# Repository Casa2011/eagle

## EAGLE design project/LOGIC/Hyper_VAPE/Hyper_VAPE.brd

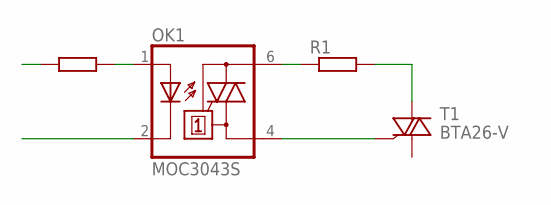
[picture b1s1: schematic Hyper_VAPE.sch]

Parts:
OK1: MOC3043S; DIL6-SMD
R1: R-EU_0411/3V; 0411V
R3: R0805
T1: BTA26-V; TOP3S-1

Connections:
unnamed: OK1.4 (A1), T1.G
unnamed: OK1.6 (A2), R1.1
unnamed: R1.2, T1.A2
unnamed: OK1.1 (A), R3.2

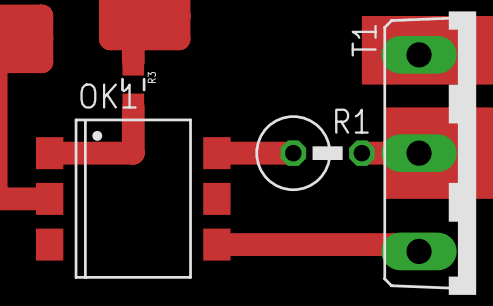
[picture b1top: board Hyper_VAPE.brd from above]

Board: 2 copper layers, 4 parts (0 on the bottom side), 4 nets.

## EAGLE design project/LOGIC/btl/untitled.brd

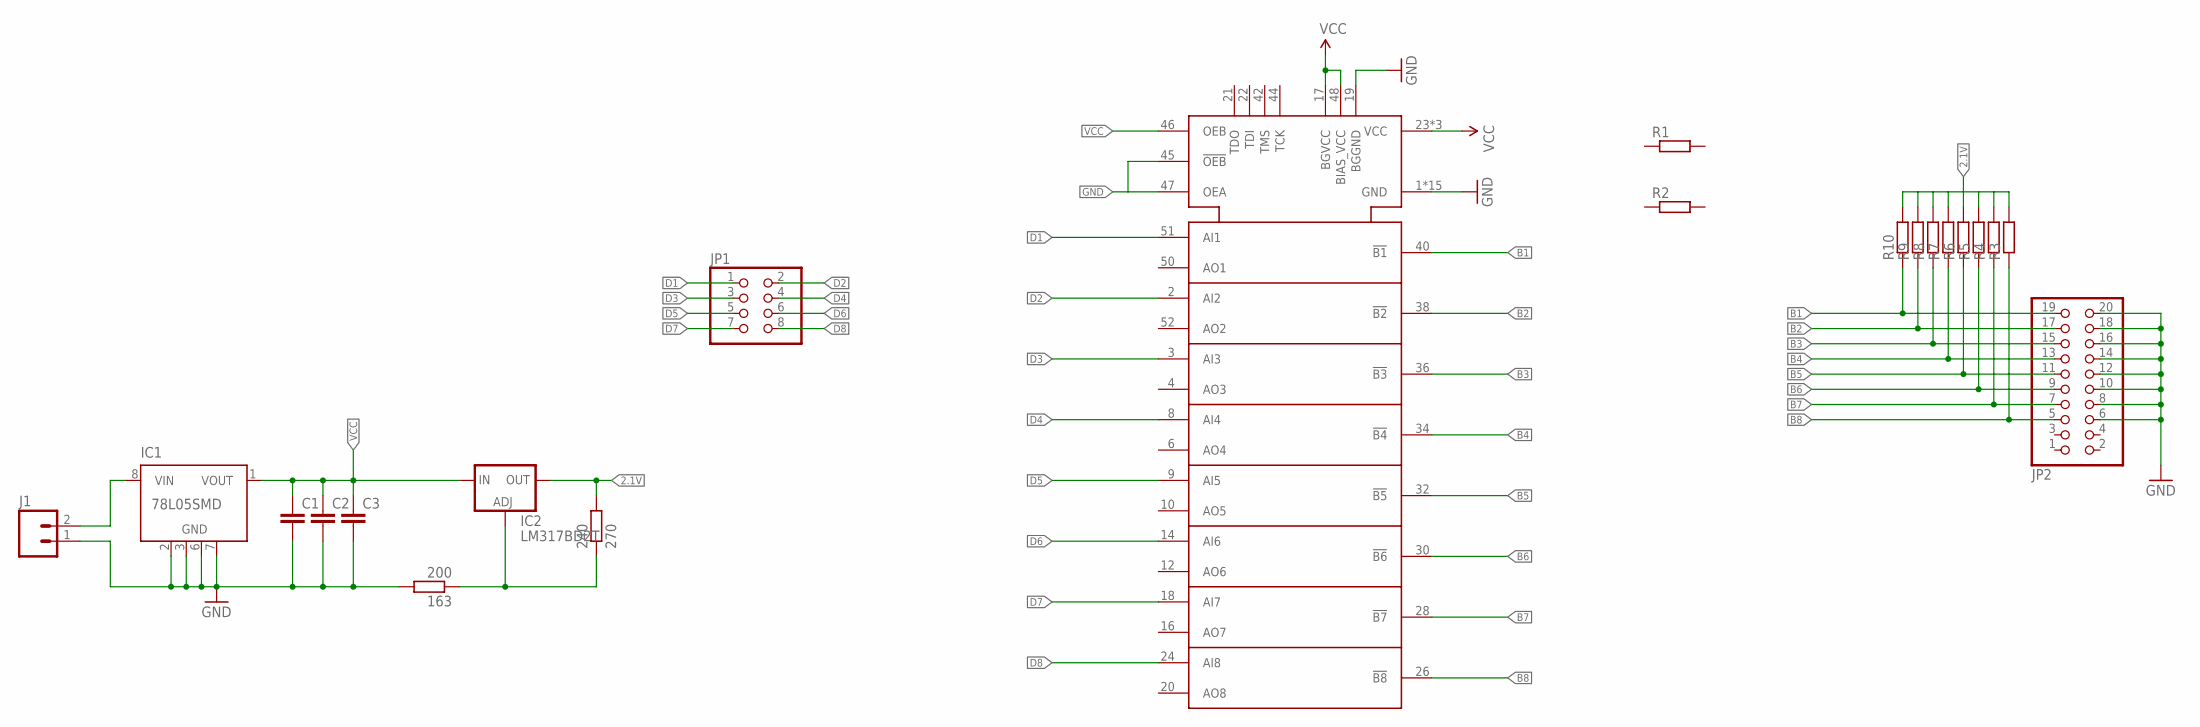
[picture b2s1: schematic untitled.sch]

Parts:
163: 200; R0805
240: 270; R0805
C1, C2, C3: CC0805; C0805
IC1: 78L05SMD; SO08
IC2: LM317BD2T; D2PACK
J1: M02LOCK_LONGPADS; 1X02_LOCK_LONGPADS
JP1: PINHD-2X04_2.54-SMD; 2X04SMD
JP2: PINHD-2X10_2.54-SMD; 2X10SMD
R1, R2, R3, R4, R5, R6, R7, R8, R9, R10: R0805
U$1: SN74FB2050; TQFP-10X10-52

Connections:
2.1V: 240.2, IC2.2 (OUT), R3.2, R4.2, R5.2, R6.2, R7.2, R8.2, R9.2, R10.2
B1: JP2.19, R10.1, U$1.40 (!B1)
B2: JP2.17, R9.1, U$1.38 (!B2)
B3: JP2.15, R8.1, U$1.36 (!B3)
B4: JP2.13, R7.1, U$1.34 (!B4)
B5: JP2.11, R6.1, U$1.32 (!B5)
B6: JP2.9, R5.1, U$1.30 (!B6)
B7: JP2.7, R4.1, U$1.28 (!B7)
B8: JP2.5, R3.1, U$1.26 (!B8)
D1: JP1.1, U$1.51 (AI1)
D2: JP1.2, U$1.2 (AI2)
D3: JP1.3, U$1.3 (AI3)
D4: JP1.4, U$1.8 (AI4)
D5: JP1.5, U$1.9 (AI5)
D6: JP1.6, U$1.14 (AI6)
D7: JP1.7, U$1.18 (AI7)
D8: JP1.8, U$1.24 (AI8)
GND: 163.2, C1.2, C2.2, C3.2, IC1.2 (GND), IC1.3 (GND), IC1.6 (GND), IC1.7 (GND), J1.1, JP2.6, JP2.8, JP2.10, JP2.12, JP2.14, JP2.16, JP2.18, JP2.20, U$1.1 (GND), U$1.5 (GND), U$1.7 (GND), U$1.11 (GND), U$1.13 (GND), U$1.15 (GND), U$1.19 (BGGND), U$1.25 (GND), U$1.27 (GND), U$1.29 (GND), U$1.31 (GND), U$1.33 (GND), U$1.35 (GND), U$1.37 (GND), U$1.39 (GND), U$1.41 (GND), U$1.45 (!OEB), U$1.47 (OEA)
unnamed: IC1.8 (VIN), J1.2
unnamed: 163.1, 240.1, IC2.1 (ADJ)
VCC: C1.1, C2.1, C3.1, IC1.1 (VOUT), IC2.3 (IN), U$1.17 (BGVCC), U$1.23 (VCC), U$1.43 (VCC), U$1.46 (OEB), U$1.48 (BIAS_VCC), U$1.49 (VCC)

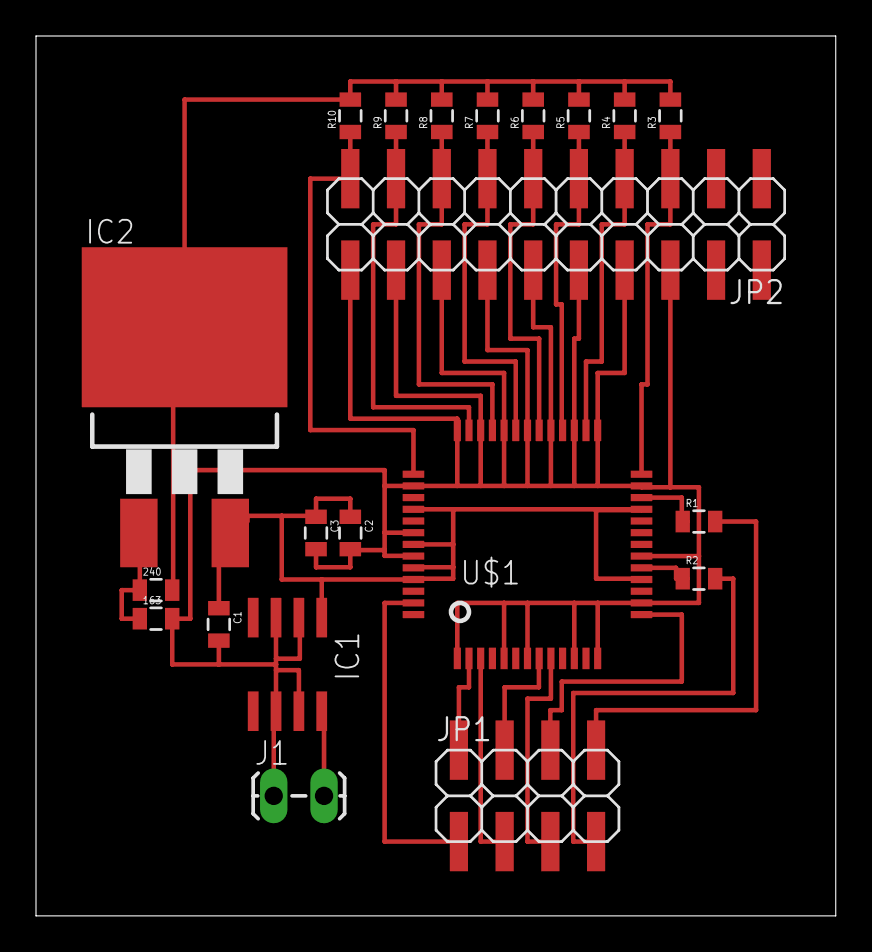
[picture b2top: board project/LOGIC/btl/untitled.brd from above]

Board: 2 copper layers, 44.4 x 48.9 mm, 21 parts (0 on the bottom side), 21 nets.

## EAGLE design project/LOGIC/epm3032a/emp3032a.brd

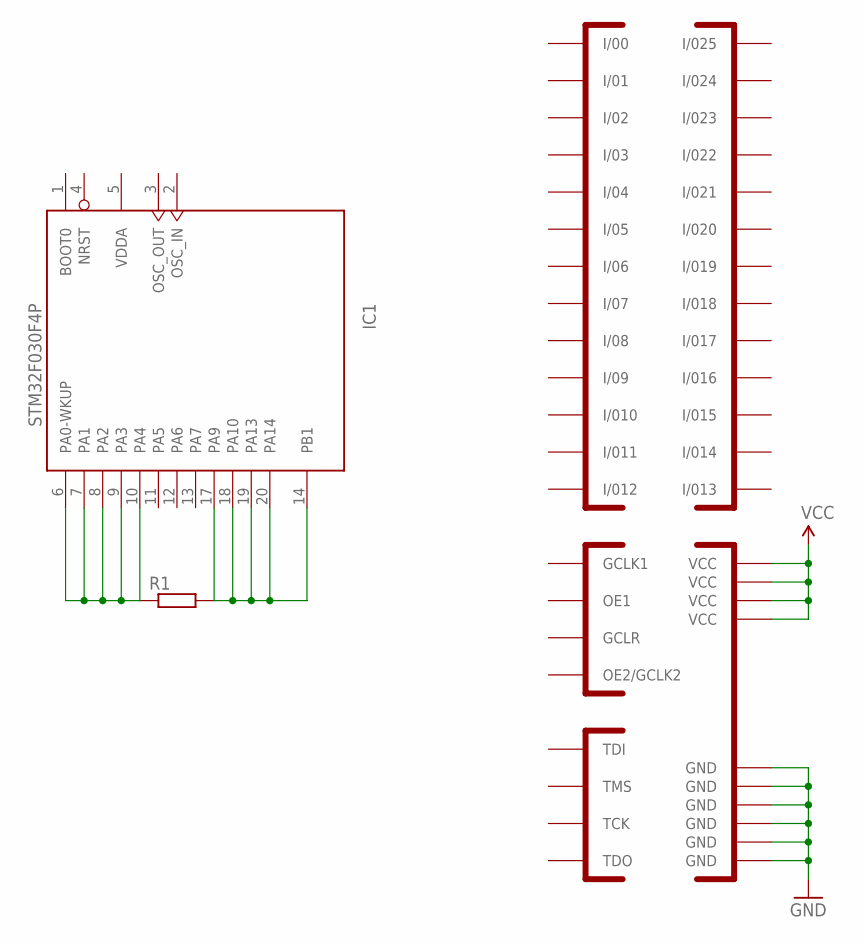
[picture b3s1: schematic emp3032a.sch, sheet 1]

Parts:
IC1: STM32F030F4P; TSSOP20-I
R1: R1206
U$1: EPM3032; TQFP44

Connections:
GCLK1: U$1.37 (GCLK1)
GCLR: U$1.39 (GCLR)
GND: U$1.4 (GND), U$1.11 (GND), U$1.16 (GND), U$1.24 (GND), U$1.30 (GND), U$1.36 (GND); also elsewhere on the board
I/00: U$1.2 (I/00)
I/01: U$1.5 (I/01)
I/02: U$1.6 (I/02)
I/03: U$1.12 (I/03)
I/04: U$1.13 (I/04)
I/05: U$1.14 (I/05)
I/06: U$1.15 (I/06)
I/07: U$1.25 (I/07)
I/08: U$1.44 (I/08)
I/09: U$1.43 (I/09)
I/010: U$1.42 (I/010)
I/011: U$1.35 (I/011)
I/012: U$1.34 (I/012)
I/013: U$1.28 (I/013)
I/014: U$1.27 (I/014)
I/015: U$1.33 (I/015)
I/016: U$1.21 (I/016)
I/017: U$1.22 (I/017)
I/018: U$1.23 (I/018)
I/019: U$1.31 (I/019)
I/020: U$1.18 (I/020)
I/021: U$1.19 (I/021)
I/022: U$1.8 (I/022)
I/023: U$1.20 (I/023)
I/024: U$1.10 (I/024)
I/025: U$1.3 (I/025)
unnamed: IC1.6 (PA0-WKUP), IC1.7 (PA1), IC1.8 (PA2), IC1.9 (PA3), IC1.10 (PA4), R1.1
unnamed: IC1.14 (PB1), IC1.17 (PA9), IC1.18 (PA10), IC1.19 (PA13), IC1.20 (PA14), R1.2
OE1: U$1.38 (OE1)
OE2/GCLK2: U$1.40 (OE2/GCLK2)
TCK: U$1.26 (TCK)
TDI: U$1.1 (TDI)
TDO: U$1.32 (TDO)
TMS: U$1.7 (TMS)
VCC: U$1.9 (VCC), U$1.17 (VCC), U$1.29 (VCC), U$1.41 (VCC)
VDD: IC1.16 (VDD)
VDDA: IC1.5 (VDDA)
VSS: IC1.15 (VSS)

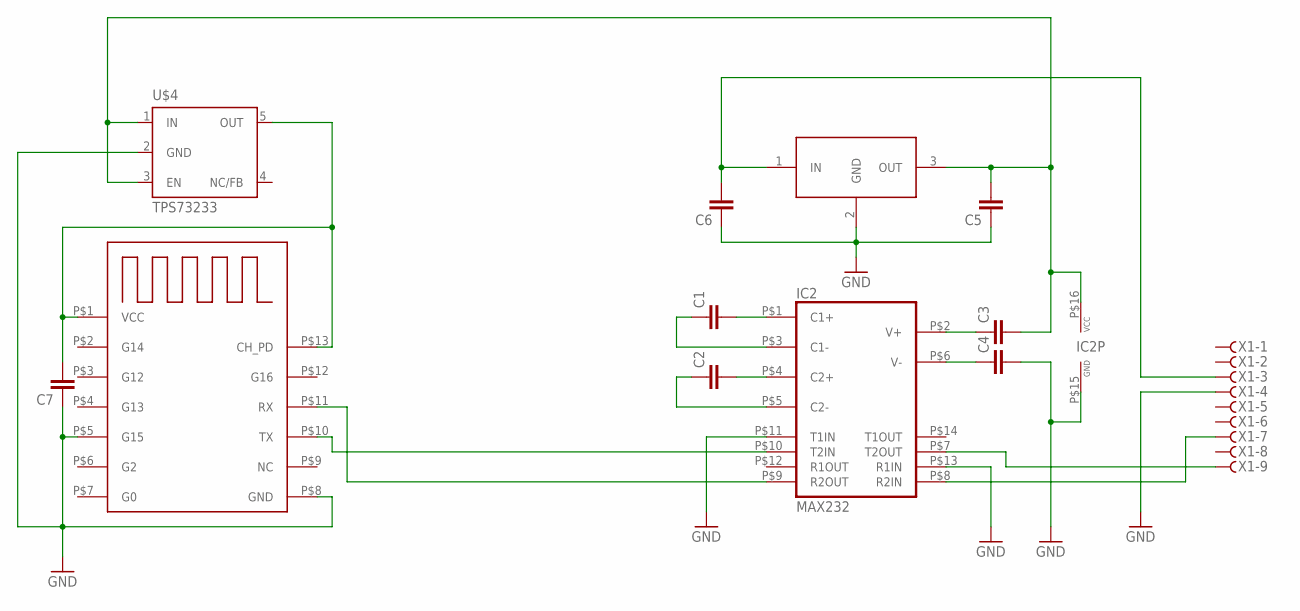
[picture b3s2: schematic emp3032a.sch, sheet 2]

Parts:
C1, C2, C3, C4, C5, C6, C7: C-EUC1206K; C1206K
IC2: MAX232; DIL16
U$2: ESP03
U$3: LM78M05BG; DPACK
U$4: TPS73233; SOT23-DBV
X1: F09HS; F09H

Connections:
GND: C4.2, C5.1, C6.1, C7.1, IC2.P$11 (T1IN), IC2.P$13 (R1IN), IC2.P$15 (GND), U$2.P$5 (G15), U$2.P$8 (GND), U$3.2 (GND), U$4.2 (GND), X1.4; also elsewhere on the board
unnamed: C2.2, IC2.P$4 (C2+)
unnamed: C2.1, IC2.P$5 (C2-)
unnamed: C1.2, IC2.P$1 (C1+)
unnamed: C1.1, IC2.P$3 (C1-)
unnamed: C3.1, IC2.P$2 (V+)
unnamed: C4.1, IC2.P$6 (V-)
unnamed: IC2.P$9 (R2OUT), U$2.P$11 (RX)
unnamed: IC2.P$7 (T2OUT), X1.9
unnamed: IC2.P$8 (R2IN), X1.7
unnamed: C6.2, U$3.1 (IN), X1.3
unnamed: IC2.P$10 (T2IN), U$2.P$10 (TX)
unnamed: C7.2, U$2.P$1 (VCC), U$2.P$13 (CH_PD), U$4.5 (OUT)
unnamed: C3.2, C5.2, IC2.P$16 (VCC), U$3.3 (OUT), U$4.1 (IN), U$4.3 (EN)

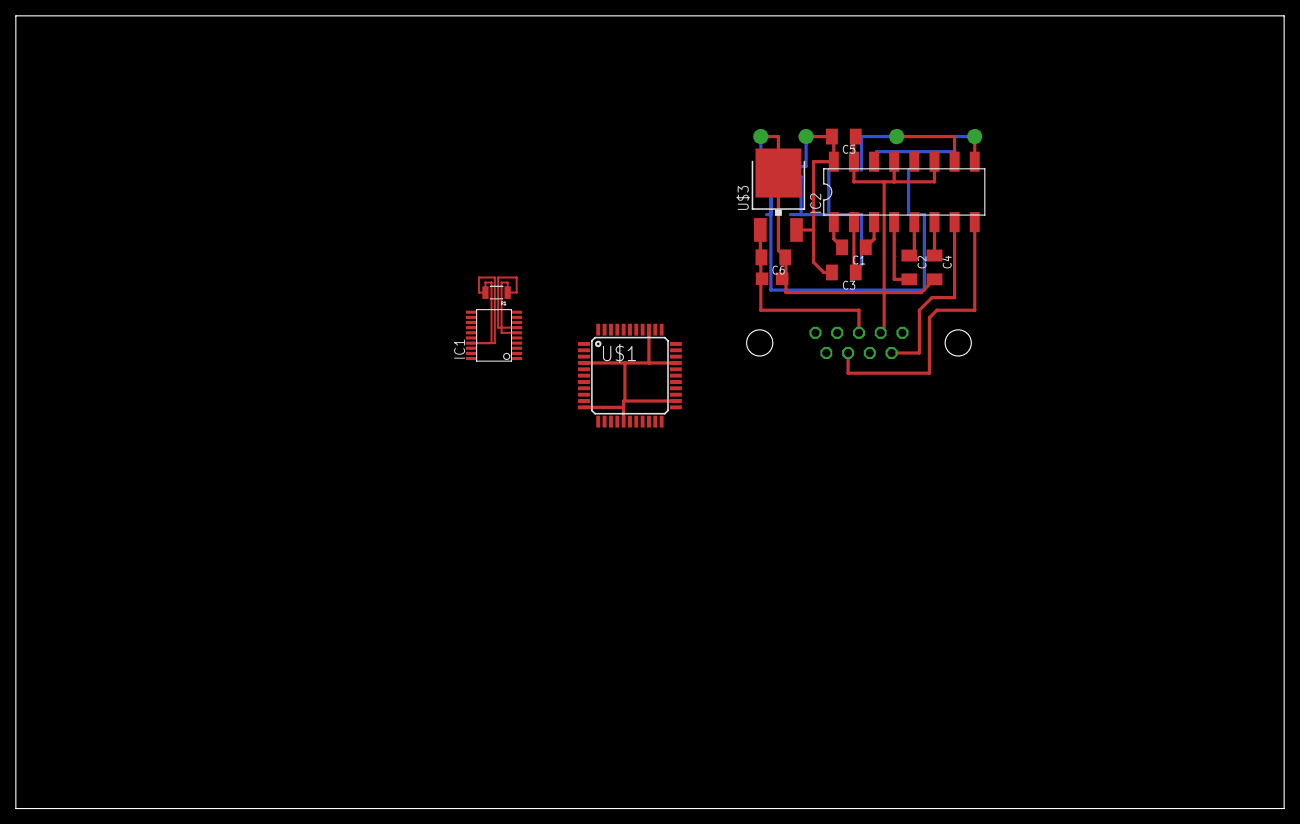
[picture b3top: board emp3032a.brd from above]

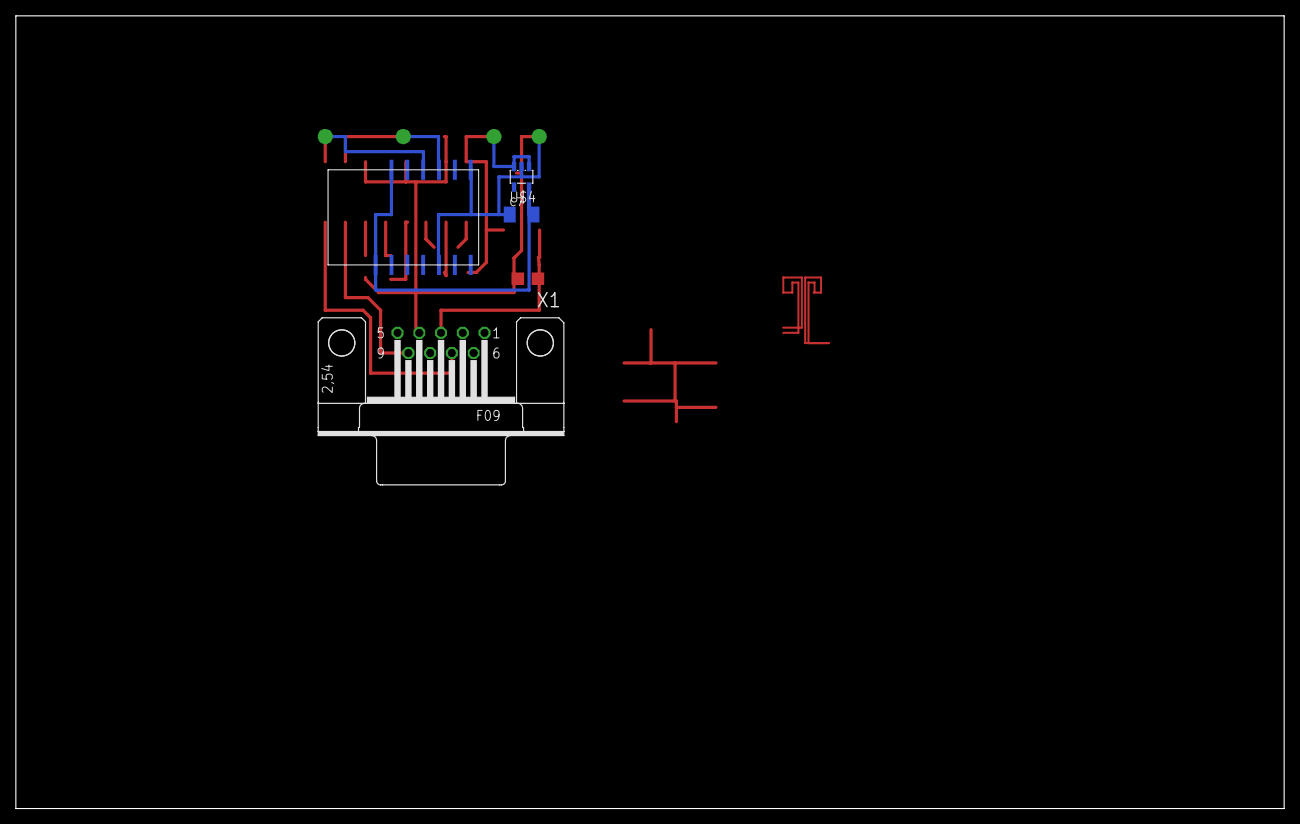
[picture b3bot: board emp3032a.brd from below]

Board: 2 copper layers, 160.0 x 100.0 mm, 15 parts (4 on the bottom side), 17 nets.

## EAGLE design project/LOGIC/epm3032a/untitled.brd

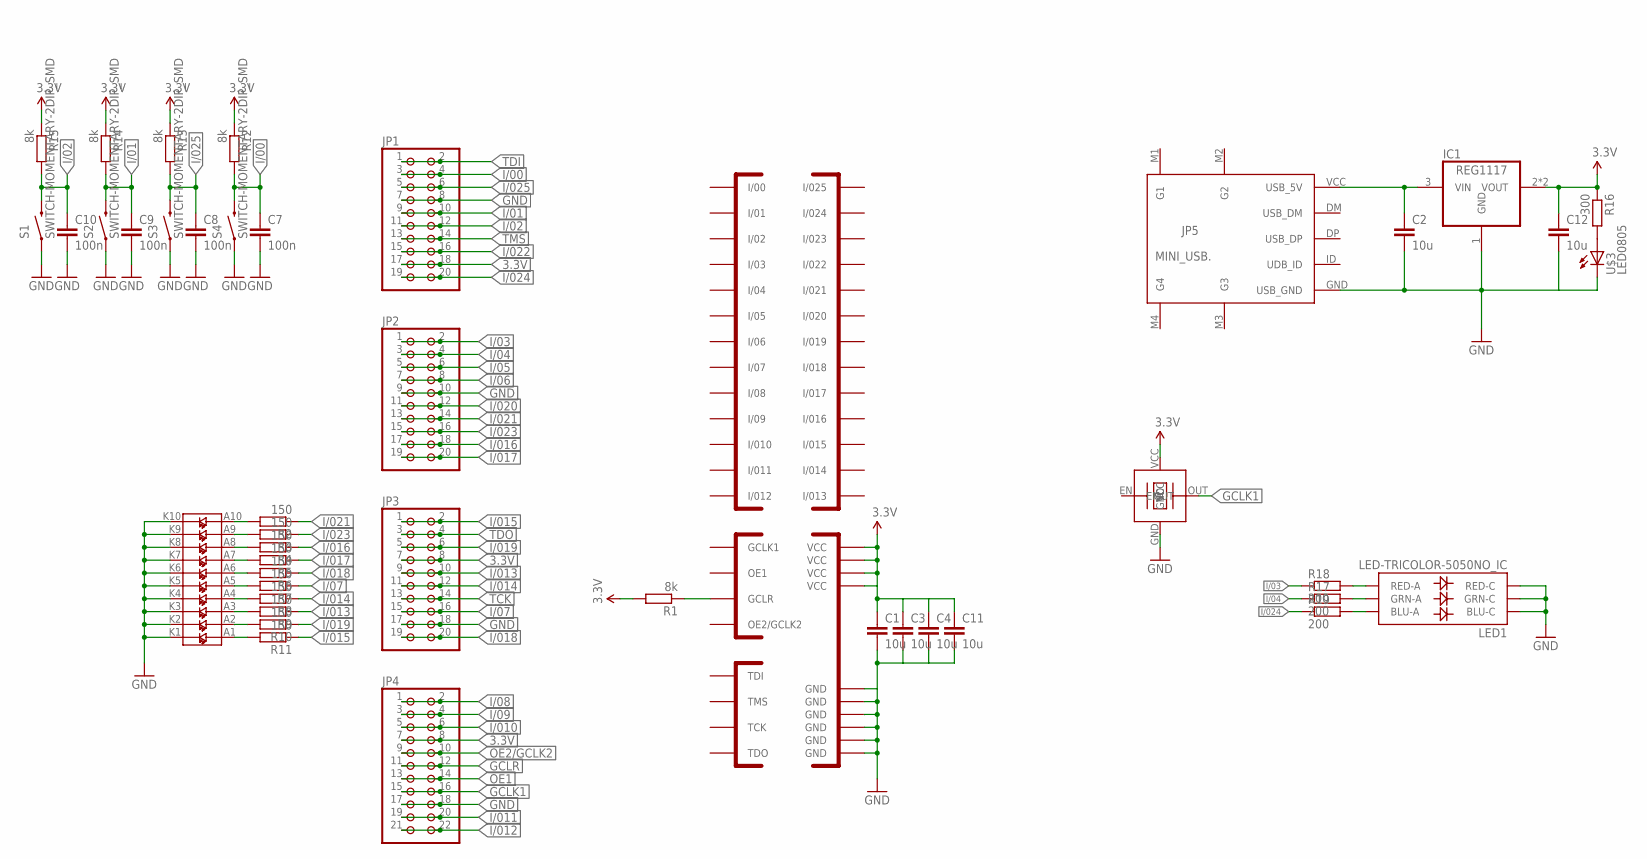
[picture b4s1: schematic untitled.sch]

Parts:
C1, C4: 10u; 0805
C2, C3, C11, C12: 10u; C0805
C7, C8, C9, C10: 100n; C0603
IC1: REG1117; SOT223
JP1, JP2, JP3: PINHD-2X10_2.54-SMD; 2X10SMD
JP4: PINHD-2X11_2.54-SMD; 2X11SMD
JP5: MINI_USB.; 32005-201
LED1: LED-TRICOLOR-5050NO_IC; LED-TRICOLOR-5050
QG1: TXC-BA; 7X5
R1, R12, R13, R14, R15: 8k; 0603
R2, R3, R4, R5, R6, R7, R8, R9, R10, R11: 150; 0603
R16: 300; 0603
R17, R18, R19: 200; 0603
S1, S2, S3, S4: SWITCH-MOMENTARY-2DIP_SMD; DIP_SMD
U$1: EPM3032; TQFP44
U$2: 10LED
U$3: LED0805; 0805-LED

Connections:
3.3V: C1.1, C3.1, C4.1, C11.1, C12.1, IC1.2 (VOUT), IC1.4 (VOUT), JP1.17, JP1.18, JP3.7, JP3.8, JP4.7, JP4.8, QG1.VCC, R1.2, R12.1, R13.1, R14.1, R15.1, R16.1, U$1.9 (VCC), U$1.17 (VCC), U$1.29 (VCC), U$1.41 (VCC)
5V: C2.1, IC1.3 (VIN), JP5.VCC (USB_5V)
GCLK1: JP4.15, JP4.16, QG1.OUT, U$1.37 (GCLK1)
GCLR: JP4.11, JP4.12, R1.1, U$1.39 (GCLR)
GND: C1.2, C2.2, C3.2, C4.2, C7.2, C8.2, C9.2, C10.2, C11.2, C12.2, IC1.1 (GND), JP1.7, JP1.8, JP2.9, JP2.10, JP3.17, JP3.18, JP4.17, JP4.18, JP5.GND (USB_GND), LED1.4 (BLU-C), LED1.5 (RED-C), LED1.6 (GRN-C), QG1.GND, S1.P$1, S1.P$2, S2.P$1, S2.P$2, S3.P$1, S3.P$2, S4.P$1, S4.P$2, U$1.4 (GND), U$1.11 (GND), U$1.16 (GND), U$1.24 (GND), U$1.30 (GND), U$1.36 (GND), U$2.K1, U$2.K2, U$2.K3, U$2.K4, U$2.K5, U$2.K6, U$2.K7, U$2.K8, U$2.K9, U$2.K10, U$3.C
I/00: C7.1, JP1.3, JP1.4, R12.2, S4.P$3, S4.P$4, U$1.2 (I/00)
I/01: C9.1, JP1.9, JP1.10, R14.2, S2.P$3, S2.P$4, U$1.5 (I/01)
I/02: C10.1, JP1.11, JP1.12, R15.2, S1.P$3, S1.P$4, U$1.6 (I/02)
I/03: JP2.1, JP2.2, R18.1, U$1.12 (I/03)
I/04: JP2.3, JP2.4, R17.1, U$1.13 (I/04)
I/05: JP2.5, JP2.6, U$1.14 (I/05)
I/06: JP2.7, JP2.8, U$1.15 (I/06)
I/07: JP3.15, JP3.16, R7.1, U$1.25 (I/07)
I/08: JP4.1, JP4.2, U$1.44 (I/08)
I/09: JP4.3, JP4.4, U$1.43 (I/09)
I/010: JP4.5, JP4.6, U$1.42 (I/010)
I/011: JP4.19, JP4.20, U$1.35 (I/011)
I/012: JP4.21, JP4.22, U$1.34 (I/012)
I/013: JP3.9, JP3.10, R9.1, U$1.28 (I/013)
I/014: JP3.11, JP3.12, R8.1, U$1.27 (I/014)
I/015: JP3.1, JP3.2, R11.1, U$1.33 (I/015)
I/016: JP2.17, JP2.18, R4.1, U$1.21 (I/016)
I/017: JP2.19, JP2.20, R5.1, U$1.22 (I/017)
I/018: JP3.19, JP3.20, R6.1, U$1.23 (I/018)
I/019: JP3.5, JP3.6, R10.1, U$1.31 (I/019)
I/020: JP2.11, JP2.12, U$1.18 (I/020)
I/021: JP2.13, JP2.14, R2.1, U$1.19 (I/021)
I/022: JP1.15, JP1.16, U$1.8 (I/022)
I/023: JP2.15, JP2.16, R3.1, U$1.20 (I/023)
I/024: JP1.19, JP1.20, R19.1, U$1.10 (I/024)
I/025: C8.1, JP1.5, JP1.6, R13.2, S3.P$3, S3.P$4, U$1.3 (I/025)
unnamed: R2.2, U$2.A10
unnamed: R3.2, U$2.A9
unnamed: R4.2, U$2.A8
unnamed: R5.2, U$2.A7
unnamed: R6.2, U$2.A6
unnamed: R7.2, U$2.A5
unnamed: R8.2, U$2.A4
unnamed: R9.2, U$2.A3
unnamed: R10.2, U$2.A2
unnamed: R11.2, U$2.A1
unnamed: LED1.2 (RED-A), R18.2
unnamed: R16.2, U$3.A
unnamed: LED1.1 (GRN-A), R17.2
unnamed: LED1.3 (BLU-A), R19.2
OE1: JP4.13, JP4.14, U$1.38 (OE1)
OE2/GCLK2: JP4.9, JP4.10, U$1.40 (OE2/GCLK2)
TCK: JP3.13, JP3.14, U$1.26 (TCK)
TDI: JP1.1, JP1.2, U$1.1 (TDI)
TDO: JP3.3, JP3.4, U$1.32 (TDO)
TMS: JP1.13, JP1.14, U$1.7 (TMS)

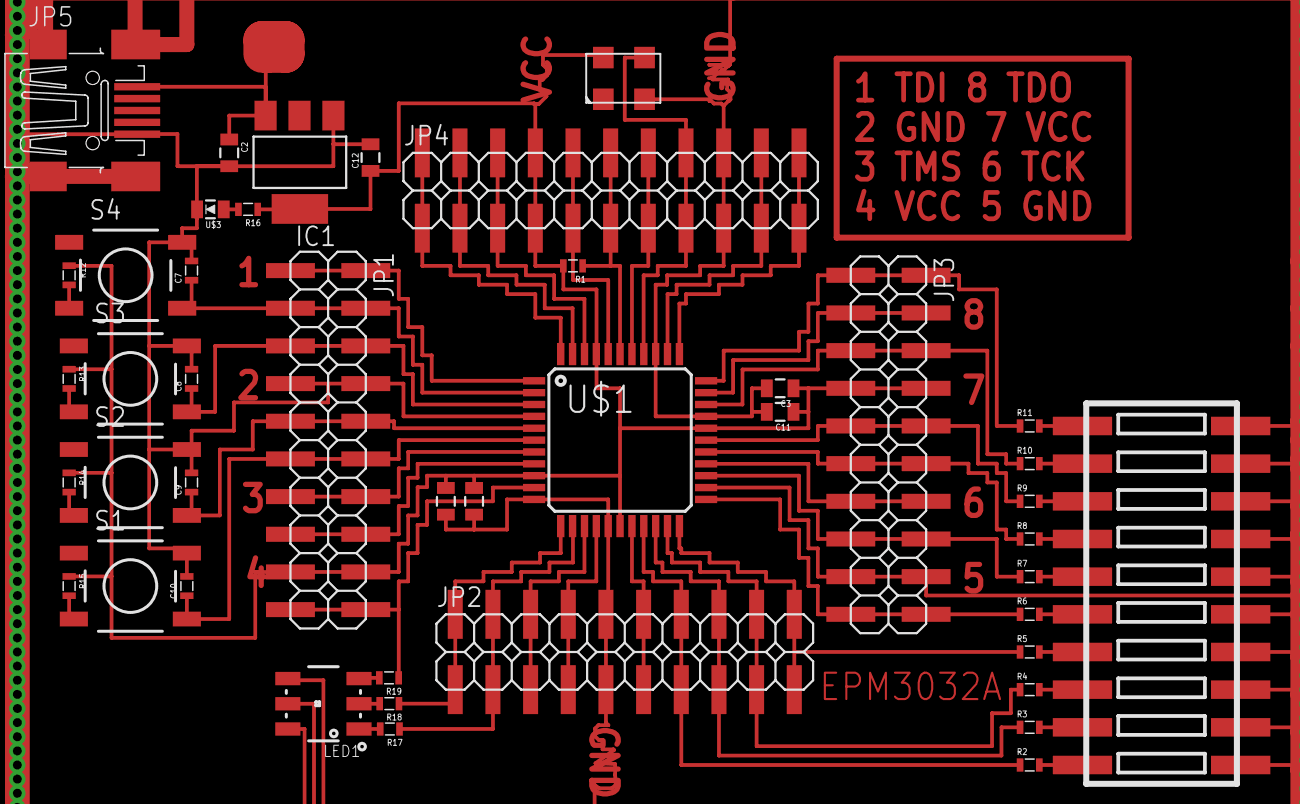
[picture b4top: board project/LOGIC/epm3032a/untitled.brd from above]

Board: 2 copper layers, 44 parts (0 on the bottom side), 51 nets.

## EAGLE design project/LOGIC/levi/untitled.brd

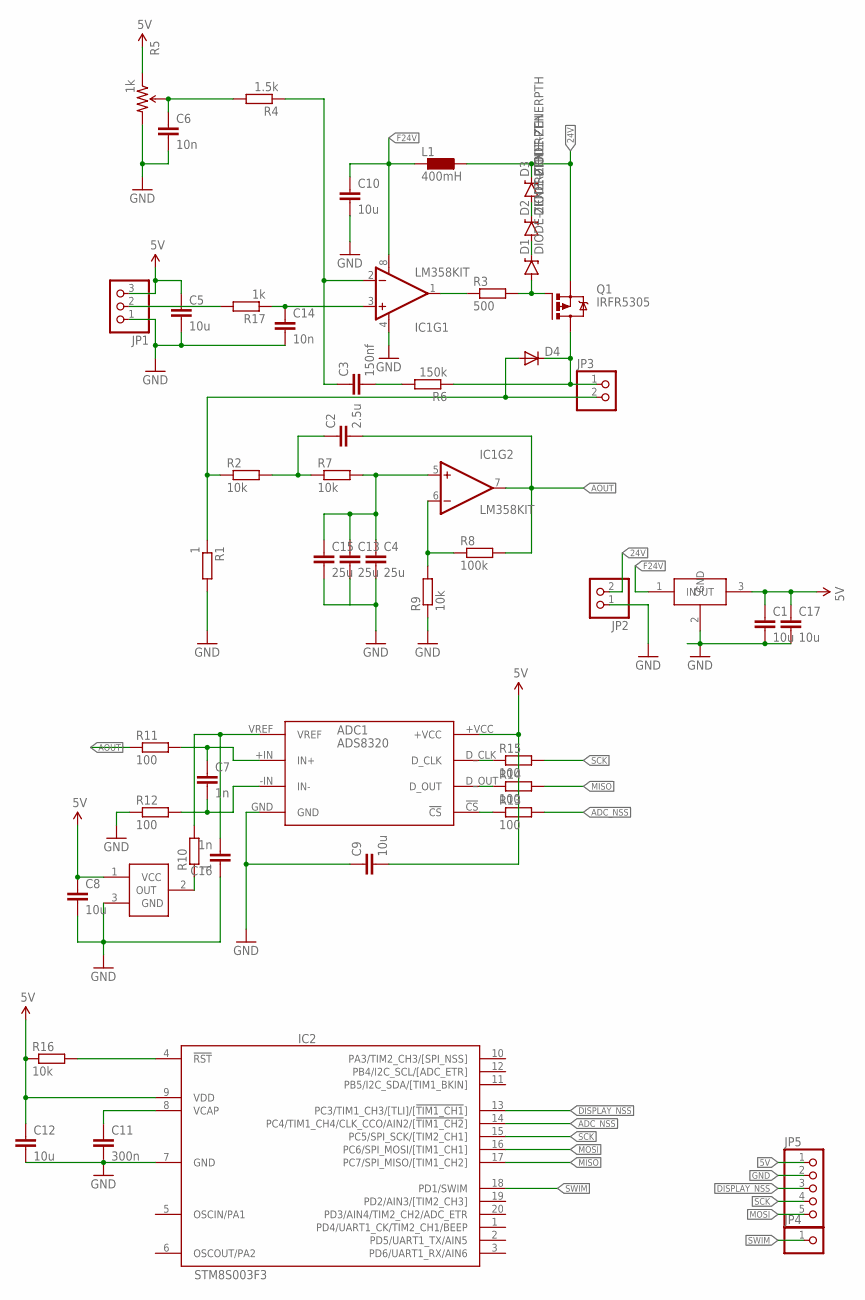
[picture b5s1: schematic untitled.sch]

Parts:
ADC1: ADS8320; S-PDSO-G8
C1, C5, C8, C9, C10, C12, C17: 10u; C0805
C2: 2.5u; C0805
C3: 150nf; C0805
C4, C13, C15: 25u; C0805
C6, C14: 10n; C0805
C7, C16: 1n; C0805
C11: 300n; C0805
D1, D2, D3: DIODE-ZENERPTH; DIODE-ZENER
D4: DIODE-MINIMELF; MINIMELF
IC1: LM358KIT; DIP08-KIT
IC2: STM8S003F3; TSSOP20
JP1: PINHD-1X3; 1X03
JP2, JP3: PINHD-1X02_2.54; 1X02
JP4: PINHD-1X01_2.54; 1X01
JP5: PINHD-1X05_2.54; 1X05
L1: 400mH; L5650M
Q1: IRFR5305; D-PAK_TO252AA
R1, R10: 1; R0805
R2, R7, R9, R16: 10k; R0805
R3: 500; R0805
R4: 1.5k; R0805
R5: 1k; TRIMPOT_PTH_S3_LOCK
R6: 150k; R0805
R8: 100k; R0805
R11, R12, R13, R14, R15: 100; R0805
R17: 1k; R0805
U$1: REF3025; SOT23
U$2: L7805C2T; D2PACK

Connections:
5V: ADC1.+VCC, C1.1, C5.1, C8.1, C9.2, C12.1, C17.1, IC2.9 (VDD), JP1.3, JP5.1, R5.1 (CCW), R16.1, U$1.1 (VCC), U$2.3 (OUT)
24V: D3.P$1 (C), JP2.2, L1.1, Q1.3 (S)
ADC_NSS: IC2.14 (PC4/TIM1_CH4/CLK_CCO/AIN2/[!TIM1_CH2!]), R13.2
AOUT: C2.2, IC1.7 (OUT), R8.2, R11.1
DISPLAY_NSS: IC2.13 (PC3/TIM1_CH3/[TLI]/[!TIM1_CH1!]), JP5.3
F24V: C10.1, IC1.8 (V+), L1.2, U$2.1 (IN)
GND: ADC1.GND, C1.2, C4.2, C5.2, C6.2, C8.2, C9.1, C10.2, C11.2, C12.2, C13.2, C14.2, C15.2, C16.1, C17.2, IC1.4 (V-), IC2.7 (GND), JP1.1, JP2.1, JP5.2, R1.2, R5.3 (CW), R9.1, R12.1, U$1.3 (GND), U$2.2 (GND)
MISO: IC2.17 (PC7/SPI_MISO/[TIM1_CH2]), R14.2
MOSI: IC2.16 (PC6/SPI_MOSI/[TIM1_CH1]), JP5.5
unnamed: IC1.1 (OUT), R3.1
unnamed: C3.2, R6.2
unnamed: D4.C, JP3.1, Q1.4 (D), R6.1
unnamed: C14.1, IC1.3 (+IN), R17.1
unnamed: C3.1, IC1.2 (-IN), R4.1
unnamed: C6.1, R4.2, R5.2 (WIPER)
unnamed: D4.A, JP3.2, R1.1, R2.1
unnamed: C2.1, R2.2, R7.1
unnamed: D1.P$2 (A), Q1.1 (G), R3.2
unnamed: C4.1, C13.1, C15.1, IC1.5 (+IN), R7.2
unnamed: R10.1, U$1.2 (OUT)
unnamed: IC1.6 (-IN), R8.1, R9.2
unnamed: ADC1.VREF, C16.2, R10.2
unnamed: D2.P$1 (C), D3.P$2 (A)
unnamed: D1.P$1 (C), D2.P$2 (A)
unnamed: ADC1.-IN (IN-), C7.2, R12.2
unnamed: ADC1.+IN (IN+), C7.1, R11.2
unnamed: C11.1, IC2.8 (VCAP)
unnamed: ADC1.D_CLK, R15.1
unnamed: ADC1.D_OUT, R14.1
unnamed: ADC1.!CS, R13.1
unnamed: IC2.4 (!RST), R16.2
unnamed: JP1.2, R17.2
SCK: IC2.15 (PC5/SPI_SCK/[TIM2_CH1]), JP5.4, R15.2
SWIM: IC2.18 (PD1/SWIM), JP4.1

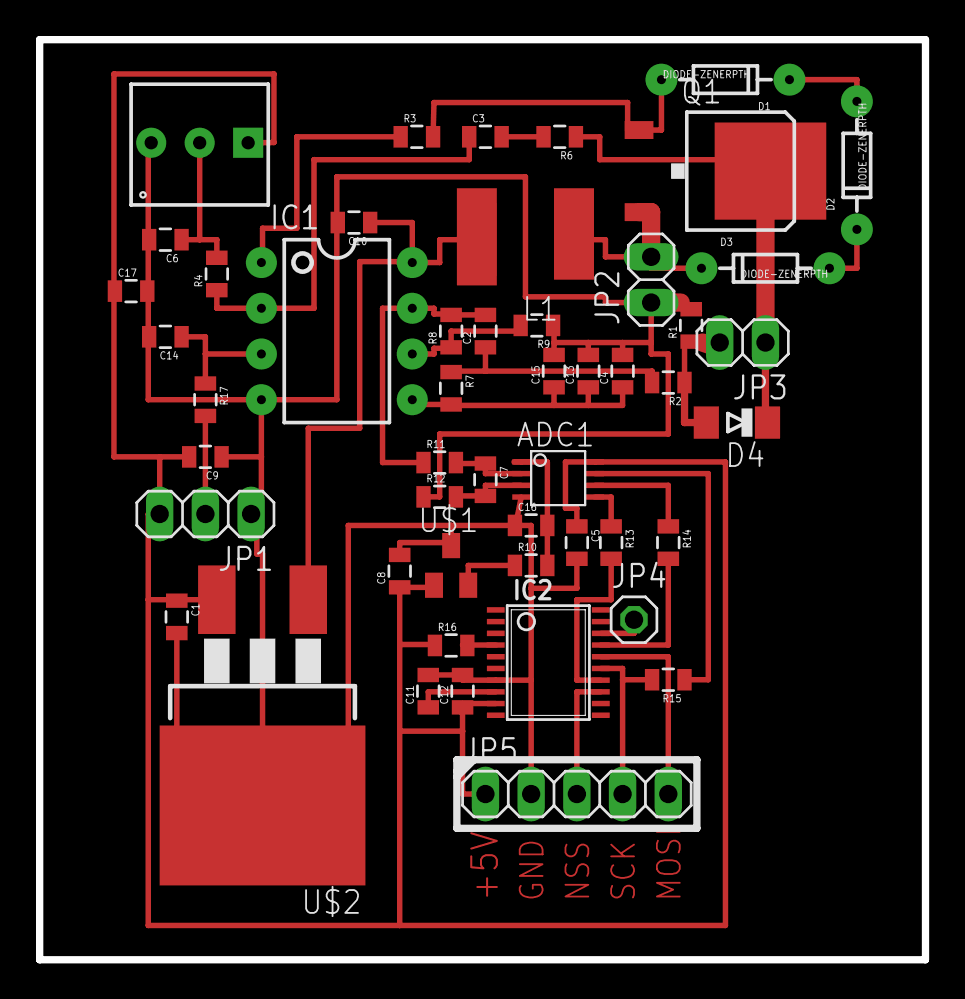
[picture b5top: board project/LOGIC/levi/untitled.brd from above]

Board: 2 copper layers, 49.2 x 51.1 mm, 50 parts (0 on the bottom side), 34 nets.

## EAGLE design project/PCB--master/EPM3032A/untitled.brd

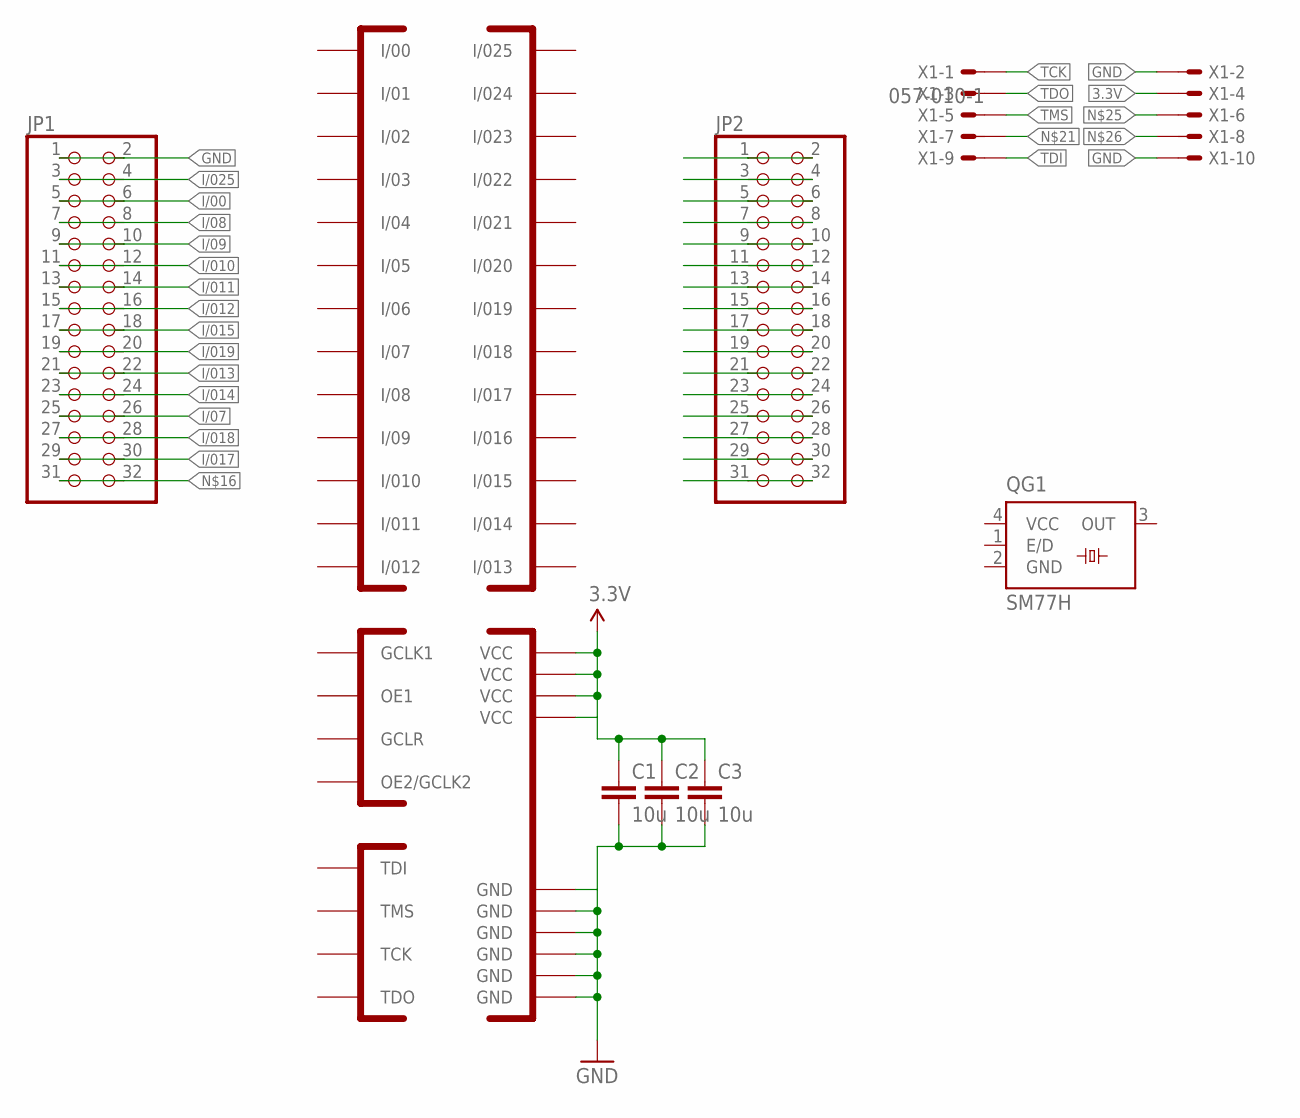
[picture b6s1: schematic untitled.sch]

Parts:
C1, C2, C3: 10u; 0805
JP1, JP2: PINHD-2X16_2.54-SMD; 2X16SMD
QG1: SM77H
U$1: EPM3032; TQFP44
X1: 057-010-1

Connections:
3.3V: C1.1, C2.1, C3.1, U$1.9 (VCC), U$1.17 (VCC), U$1.29 (VCC), U$1.41 (VCC), X1.4
GCLK1: U$1.37 (GCLK1)
GCLR: U$1.39 (GCLR)
GND: C1.2, C2.2, C3.2, JP1.1, JP1.2, QG1.2 (GND), U$1.4 (GND), U$1.11 (GND), U$1.16 (GND), U$1.24 (GND), U$1.30 (GND), U$1.36 (GND), X1.2, X1.10
I/00: JP1.5, JP1.6, U$1.2 (I/00)
I/01: U$1.5 (I/01)
I/02: U$1.6 (I/02)
I/03: U$1.12 (I/03)
I/04: U$1.13 (I/04)
I/05: U$1.14 (I/05)
I/06: U$1.15 (I/06)
I/07: JP1.25, JP1.26, U$1.25 (I/07)
I/08: JP1.7, JP1.8, U$1.44 (I/08)
I/09: JP1.9, JP1.10, U$1.43 (I/09)
I/010: JP1.11, JP1.12, U$1.42 (I/010)
I/011: JP1.13, JP1.14, U$1.35 (I/011)
I/012: JP1.15, JP1.16, U$1.34 (I/012)
I/013: JP1.21, JP1.22, U$1.28 (I/013)
I/014: JP1.23, JP1.24, U$1.27 (I/014)
I/015: JP1.17, JP1.18, U$1.33 (I/015)
I/016: U$1.21 (I/016)
I/017: JP1.29, JP1.30, U$1.22 (I/017)
I/018: JP1.27, JP1.28, U$1.23 (I/018)
I/019: JP1.19, JP1.20, U$1.31 (I/019)
I/020: U$1.18 (I/020)
I/021: U$1.19 (I/021)
I/022: U$1.8 (I/022)
I/023: U$1.20 (I/023)
I/024: U$1.10 (I/024)
I/025: JP1.3, JP1.4, U$1.3 (I/025)
unnamed: JP2.7, JP2.8
unnamed: JP2.27, JP2.28
unnamed: JP2.31, JP2.32
unnamed: JP2.23, JP2.24
unnamed: JP2.19, JP2.20
unnamed: JP2.15, JP2.16
unnamed: JP2.1, JP2.2
unnamed: JP2.3, JP2.4
unnamed: JP2.11, JP2.12
unnamed: JP2.5, JP2.6
unnamed: JP2.9, JP2.10
unnamed: JP2.13, JP2.14
unnamed: JP2.17, JP2.18
unnamed: JP2.21, JP2.22
unnamed: JP2.25, JP2.26
unnamed: JP1.31, JP1.32
unnamed: JP2.29, JP2.30
OE1: U$1.38 (OE1)
OE2/GCLK2: U$1.40 (OE2/GCLK2)
TCK: U$1.26 (TCK), X1.1
TDI: U$1.1 (TDI), X1.9
TDO: U$1.32 (TDO), X1.3
TMS: U$1.7 (TMS), X1.5
VCC: QG1.4 (VCC)

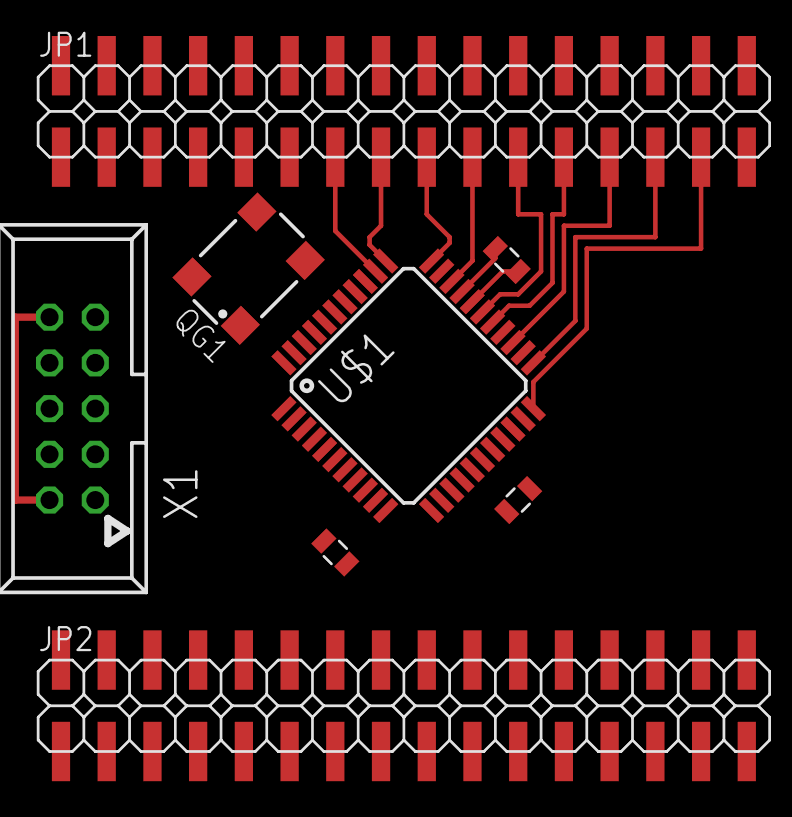
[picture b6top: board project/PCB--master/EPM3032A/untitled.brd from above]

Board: 2 copper layers, 8 parts (0 on the bottom side), 37 nets.

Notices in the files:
parts and their libraries:
SparkFun-Aesthetics: Licensing: Creative Commons ShareAlike 4.0 International - https://creativecommons.org/licenses/by-sa/4.0
